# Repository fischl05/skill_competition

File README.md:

# skill_competition

## Task 3 - Embedded Programming with STM32

##### Audio interface

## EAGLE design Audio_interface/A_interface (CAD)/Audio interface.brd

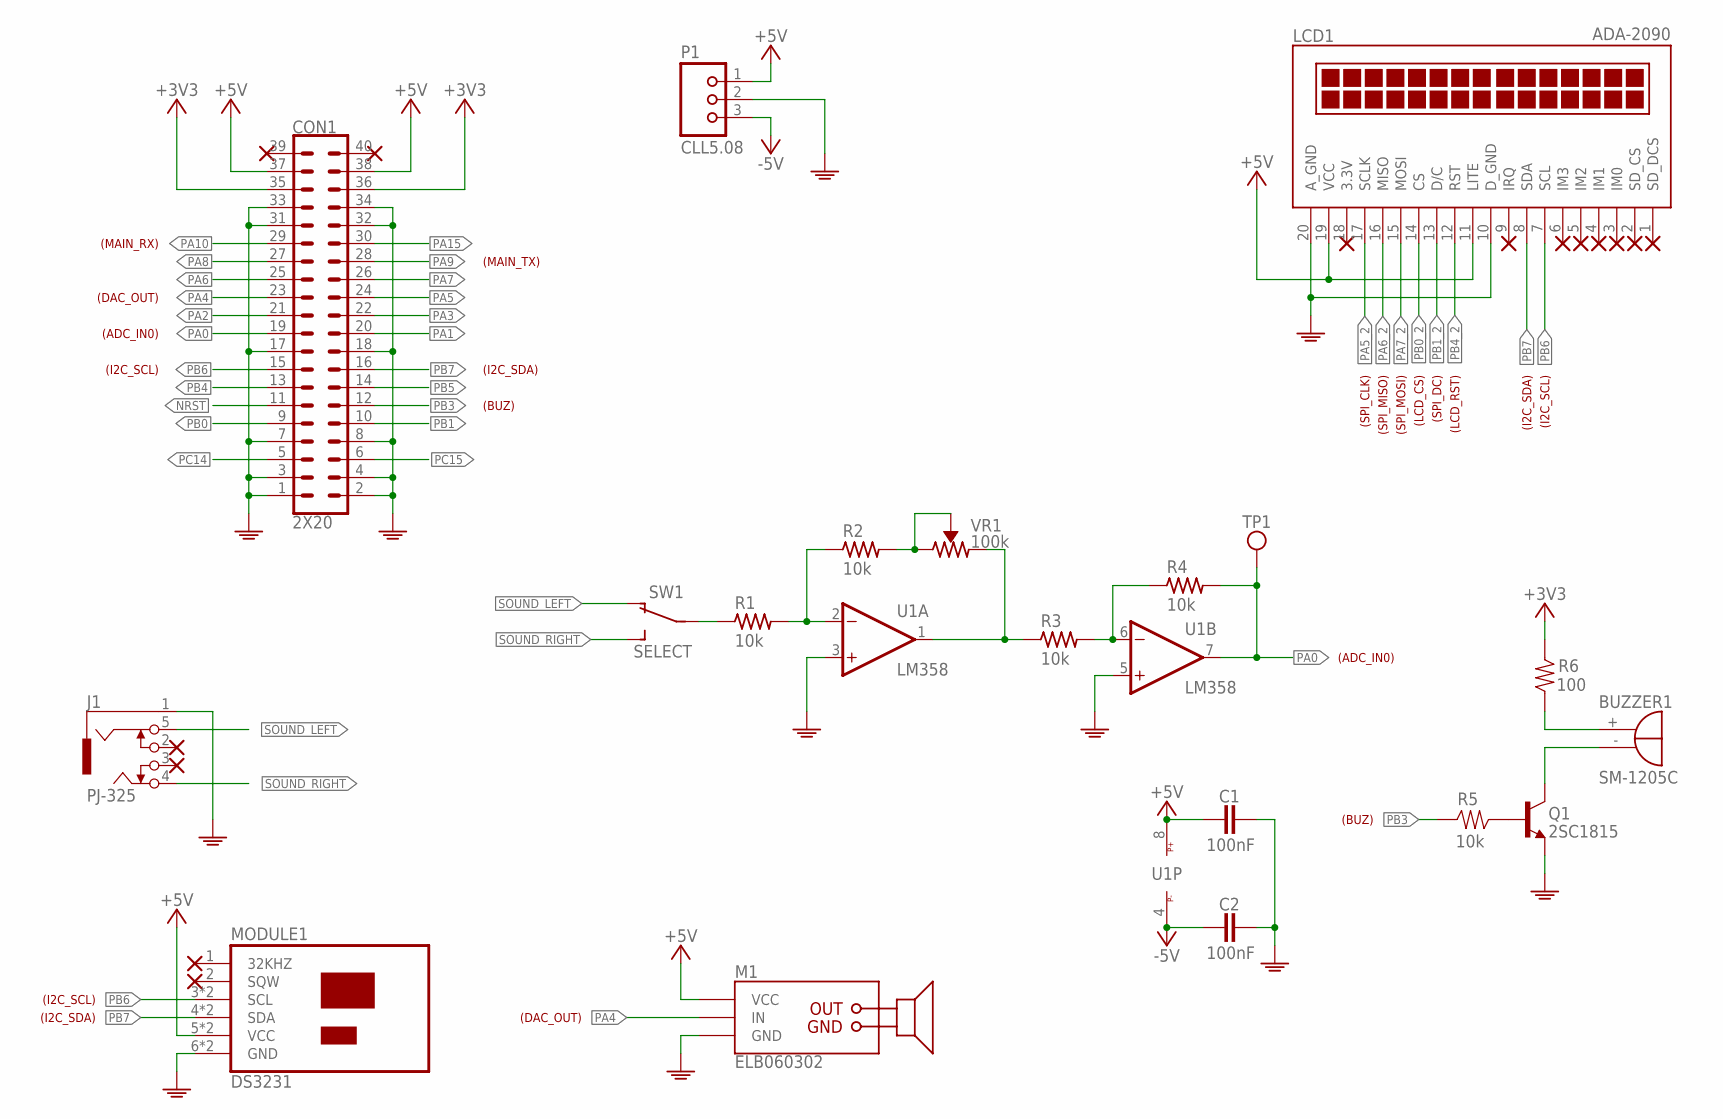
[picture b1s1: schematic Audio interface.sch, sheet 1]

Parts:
BUZZER1: SM-1205C
C1, C2: 100nF; C2012
CON1: 2X20; 2X20_VER3DEFORMATION
J1: PJ-325
LCD1: ADA-2090; TOUCH_SCREEN
M1: ELB060302; MODULE(ELB060302)
MODULE1: DS3231; MODULE(DS3231)
P1: CLL5.08; TERMINAL(CLL5.08-03P)
Q1: 2SC1815; SOT23
R1, R2, R3, R4, R5: 10k; 2012
R6: 100; 2012
SW1: SELECT; SW(MSL-1C2P)
TP1: TP_(LC-2-G); TP(LC-2-G)
U1: LM358; SO8(150MIL)
VR1: 100k; RTRIM(VZ067TL7)

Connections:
+3V3: CON1.35, CON1.36, R6.2; also elsewhere on the board
+5V: C1.1, CON1.37, CON1.38, LCD1.11 (LITE), LCD1.19 (VCC), M1.2 (VCC), MODULE1.5 (VCC), MODULE1.9 (VCC), P1.1, U1.8 (P+)
-5V: C2.1, P1.3, U1.4 (P-)
GND: C1.2, C2.2, CON1.1, CON1.2, CON1.3, CON1.4, CON1.7, CON1.8, CON1.17, CON1.18, CON1.31, CON1.32, CON1.33, CON1.34, J1.1 (GND), LCD1.10 (D_GND), LCD1.20 (A_GND), M1.3 (GND), MODULE1.6 (GND), MODULE1.10 (GND), P1.2, Q1.2 (E), U1.3 (+IN), U1.5 (+IN); also elsewhere on the board
unnamed: BUZZER1.+, R6.1
unnamed: BUZZER1.-, Q1.3 (C)
unnamed: Q1.1 (B), R5.1
unnamed: R1.2, R2.1, U1.2 (-IN)
unnamed: R2.2, VR1.TAP (WIPER), VR1.TOP (CW)
unnamed: R1.1, SW1.2
unnamed: R3.1, U1.1 (OUT), VR1.BOT (CCW)
unnamed: R3.2, R4.1, U1.6 (-IN)
NRST: CON1.11; also elsewhere on the board
PA0: CON1.19, R4.2, TP1.1, U1.7 (OUT)
PA1: CON1.20
PA2: CON1.21
PA3: CON1.22
PA4: CON1.23, M1.1 (IN)
PA5: CON1.24
PA5_2: LCD1.17 (SCLK); also elsewhere on the board
PA6: CON1.25
PA6_2: LCD1.16 (MISO); also elsewhere on the board
PA7: CON1.26
PA7_2: LCD1.15 (MOSI); also elsewhere on the board
PA8: CON1.27
PA9: CON1.28; also elsewhere on the board
PA10: CON1.29; also elsewhere on the board
PA15: CON1.30
PB0: CON1.9
PB0_2: LCD1.14 (CS); also elsewhere on the board
PB1: CON1.10
PB1_2: LCD1.13 (D/C); also elsewhere on the board
PB3: CON1.12, R5.2
PB4: CON1.13
PB4_2: LCD1.12 (RST); also elsewhere on the board
PB5: CON1.14
PB6: CON1.15, LCD1.7 (SCL), MODULE1.3 (SCL), MODULE1.7 (SCL)
PB7: CON1.16, LCD1.8 (SDA), MODULE1.4 (SDA), MODULE1.8 (SDA)
PC14: CON1.5
PC15: CON1.6
SOUND_LEFT: J1.5 (SP1), SW1.1 (O)
SOUND_RIGHT: J1.4 (SP2), SW1.3 (S)

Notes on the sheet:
(DAC_OUT)
(I2C_SCL)
(I2C_SDA)
(ADC_IN0)
(BUZ)
(SPI_CLK)
(SPI_MISO)
(SPI_MOSI)
(LCD_CS)
(SPI_DC)
(LCD_RST)
(MAIN_TX)
(MAIN_RX)

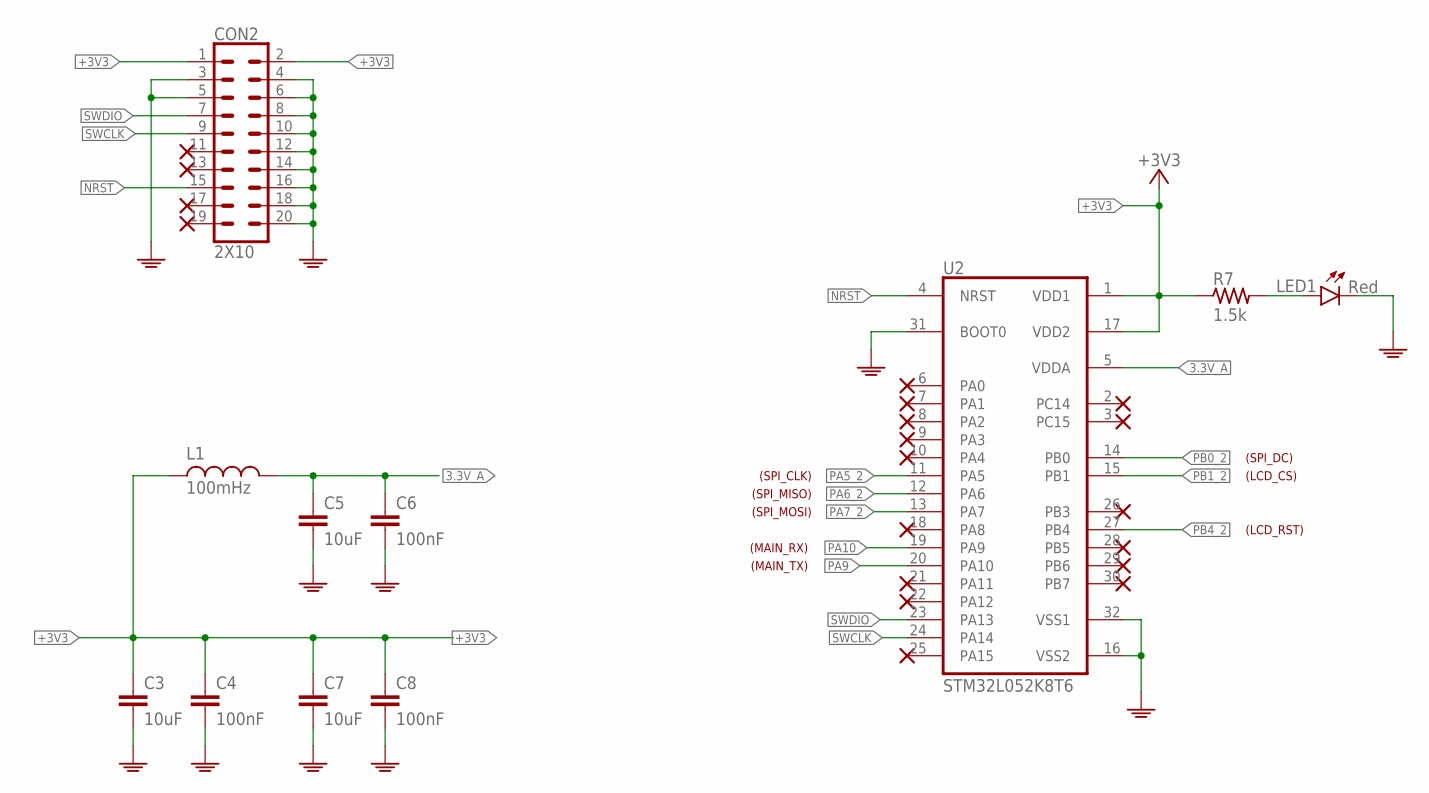
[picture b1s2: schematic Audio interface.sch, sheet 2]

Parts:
C3, C5, C7: 10uF; C0603K
C4, C6, C8: 100nF; C2012
CON2: 2X10; 2X10(MALE)
L1: 100mHz; C0603K
LED1: Red; CHIP_0805(LED)
R7: 1.5k; 2012
U2: STM32L052K8T6; LQFP32

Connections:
3.3V_A: C5.1, C6.1, L1.2, U2.5 (VDDA)
+3V3: C3.1, C4.1, C7.1, C8.1, CON2.1, CON2.2, L1.1, R7.1, U2.1 (VDD1), U2.17 (VDD2); also elsewhere on the board
GND: C3.2, C4.2, C5.2, C6.2, C7.2, C8.2, CON2.3, CON2.4, CON2.5, CON2.6, CON2.8, CON2.10, CON2.12, CON2.14, CON2.16, CON2.18, CON2.20, LED1.1 (C), U2.16 (VSS2), U2.31 (BOOT0), U2.32 (VSS1); also elsewhere on the board
unnamed: LED1.2 (A), R7.2
NRST: CON2.15, U2.4 (NRST); also elsewhere on the board
PA5_2: U2.11 (PA5); also elsewhere on the board
PA6_2: U2.12 (PA6); also elsewhere on the board
PA7_2: U2.13 (PA7); also elsewhere on the board
PA9: U2.20 (PA10); also elsewhere on the board
PA10: U2.19 (PA9); also elsewhere on the board
PB0_2: U2.14 (PB0); also elsewhere on the board
PB1_2: U2.15 (PB1); also elsewhere on the board
PB4_2: U2.27 (PB4); also elsewhere on the board
SWCLK: CON2.9, U2.24 (PA14)
SWDIO: CON2.7, U2.23 (PA13)

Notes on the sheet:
(MAIN_TX)
(MAIN_RX)
(SPI_CLK)
(SPI_MISO)
(SPI_MOSI)
(LCD_CS)
(SPI_DC)
(LCD_RST)

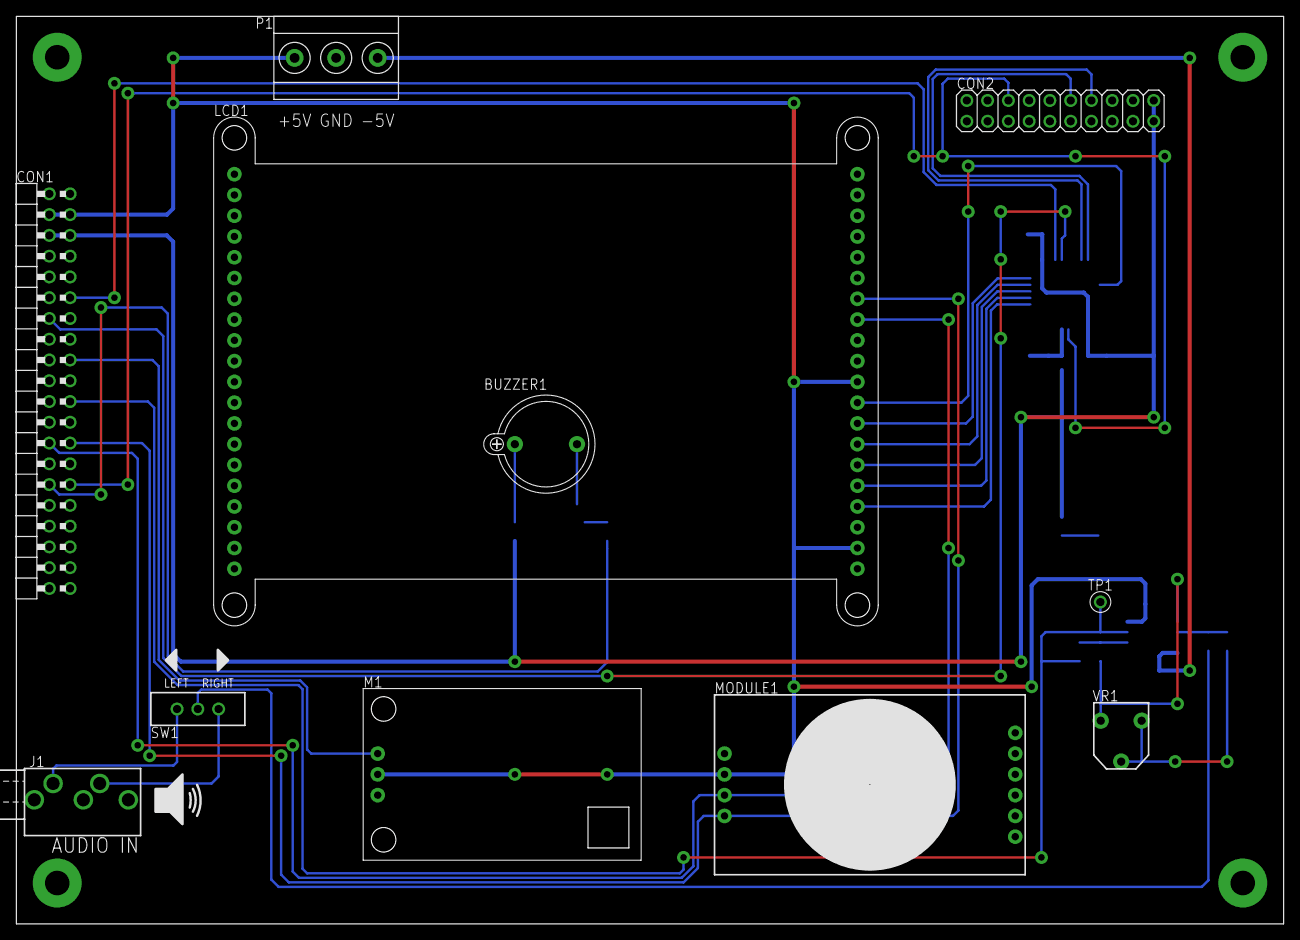
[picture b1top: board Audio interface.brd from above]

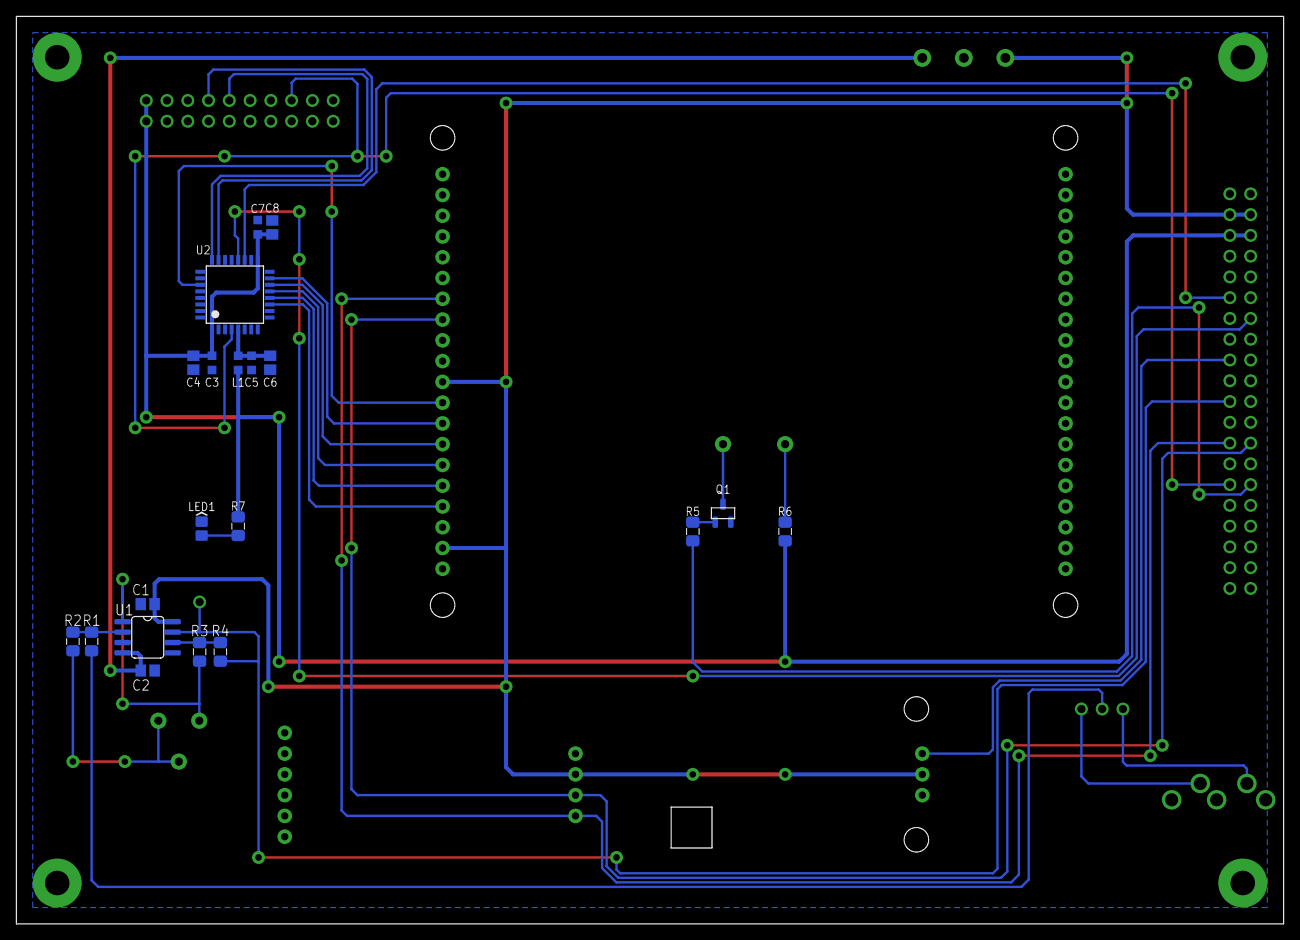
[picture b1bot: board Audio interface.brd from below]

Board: 2 copper layers, 155.0 x 111.0 mm, 31 parts (20 on the bottom side), 32 nets.

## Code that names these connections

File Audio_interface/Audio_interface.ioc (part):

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Mcu.Name=STM32L052K(6-8)Tx
Mcu.Package=LQFP32
Mcu.UserName=STM32L052K6Tx
PA0.GPIOParameters=GPIO_Label
PA0.GPIO_Label=SOUND_IN
PA0.Mode=IN0
PA0.Signal=ADC_IN0
PA4.Signal=COMP_DAC1_group
PA5.Mode=Full_Duplex_Master
PA5.Signal=SPI1_SCK
PA6.Mode=Full_Duplex_Master
PA6.Signal=SPI1_MISO
PA7.Mode=Full_Duplex_Master
PA7.Signal=SPI1_MOSI
PB0.GPIOParameters=GPIO_Speed,GPIO_Label
PB0.GPIO_Label=LCD_CS
PB0.GPIO_Speed=GPIO_SPEED_FREQ_VERY_HIGH
PB0.Signal=GPIO_Output
PB1.GPIOParameters=GPIO_Speed,GPIO_Label
PB1.GPIO_Label=LCD_DC
PB1.GPIO_Speed=GPIO_SPEED_FREQ_VERY_HIGH
PB1.Signal=GPIO_Output
PB3.GPIOParameters=GPIO_Speed,GPIO_Label
PB3.GPIO_Label=BUZ
PB3.GPIO_Speed=GPIO_SPEED_FREQ_VERY_HIGH
PB3.Signal=GPIO_Output
PB4.GPIOParameters=GPIO_Speed,GPIO_Label
PB4.GPIO_Label=LCD_RST
PB4.GPIO_Speed=GPIO_SPEED_FREQ_VERY_HIGH
PB4.Signal=GPIO_Output
PB6.GPIOParameters=GPIO_FM6,GPIO_Pu
PB6.GPIO_FM6=__NULL
PB6.GPIO_Pu=GPIO_PULLUP
PB6.Mode=I2C
PB6.Signal=I2C1_SCL
PB7.GPIOParameters=GPIO_Pu,GPIO_FM7
PB7.GPIO_FM7=__NULL
PB7.GPIO_Pu=GPIO_PULLUP
PB7.Mode=I2C
PB7.Signal=I2C1_SDA
RCC.SYSCLKFreq_VALUE=32000000
RCC.SYSCLKSource=RCC_SYSCLKSOURCE_PLLCLK
board=custom

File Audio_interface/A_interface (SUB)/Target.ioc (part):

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Mcu.Name=STM32L052K(6-8)Tx
Mcu.Package=LQFP32
Mcu.UserName=STM32L052K8Tx
PA10.Mode=Asynchronous
PA10.Signal=USART1_RX
PA13.Mode=Serial_Wire
PA13.Signal=SYS_SWDIO
PA14.Mode=Serial_Wire
PA14.Signal=SYS_SWCLK
PA5.Mode=Full_Duplex_Master
PA5.Signal=SPI1_SCK
PA6.Mode=Full_Duplex_Master
PA6.Signal=SPI1_MISO
PA7.Mode=Full_Duplex_Master
PA7.Signal=SPI1_MOSI
PA9.Mode=Asynchronous
PA9.Signal=USART1_TX
PB0.GPIOParameters=GPIO_Speed,GPIO_Label
PB0.GPIO_Label=SPI_DC
PB0.GPIO_Speed=GPIO_SPEED_FREQ_VERY_HIGH
PB0.Signal=GPIO_Output
PB1.GPIOParameters=GPIO_Speed,GPIO_Label
PB1.GPIO_Label=LCD_CS
PB1.GPIO_Speed=GPIO_SPEED_FREQ_VERY_HIGH
PB1.Signal=GPIO_Output
PB4.GPIOParameters=GPIO_Speed,GPIO_Label
PB4.GPIO_Label=LCD_RST
PB4.GPIO_Speed=GPIO_SPEED_FREQ_VERY_HIGH
PB4.Signal=GPIO_Output
RCC.SYSCLKFreq_VALUE=32000000
RCC.SYSCLKSource=RCC_SYSCLKSOURCE_PLLCLK
board=custom

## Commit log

2023-05-15 CPU setting
    Initial CPU setting
2023-05-30 tft lcd setting
    tft lcd setting
2023-06-08 library update
    touch screen library update
2023-06-26 update project
    project name : Audio interface
2023-07-04 Audio interface
    make Audi interface with STM32l052k6t6
2023-07-13 DIY Audio_interface
    for skill competition
2023-07-13 DIY Audio_interface
    for skill competition (sub MCU code)
2023-07-15 DIY Audio Interface
    for skill competition
2023-07-29 Audio interface
    for skill competition (DIY)
2023-08-05 change task
    for skill competiton Task
2023-08-07 skill competition
    Task name: Add password function
2023-08-20 2023 skill competition
    Task 3 Embedded programing
    change task
2023-08-20 skill competition
    system tester
2023-08-27 Task 3
    subject: digital clock
2023-08-27 Task 3
    subject: door management
2023-09-01 subject: smart window
    skill competition: change task
2023-09-01 Task 3
    change Task
2023-09-02 change task for skill competition
    subject: air conditioner
2023-09-03 subject: air conditioner
    for skill competition
2023-09-03 Task 3
    subject: air conditioner
2023-09-06 Task 3
    subjec: wash machin
2023-09-09 Task 3
    subject: elevator
    (skill competition change task)
2023-09-17 subject: scheduler
    for skill competition
